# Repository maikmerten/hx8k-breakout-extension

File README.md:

# hx8k-breakout-extension
A PCB with SRAM, buttons, LEDs and some pmod-compatible connectors for the Lattice HX8K Breakout Board

**Please notice**: This PCB only carries SRAM with a data bus width of 8 bits. This is pretty narrow and can be performance-limiting. Also, let's be honest, this PCB layout is somewhat wacky. Perhaps you might consider building [a more recent design with 16-bit SRAM](https://github.com/maikmerten/hx8k-sram16-extension) instead.

## BOM

| Component | Description | Qty. |
|-----------|-------------|------|
| U1 | 4 MBit SRAM chip, 512Kx8, AS7C34096A, 10ns recommended, TSOP-II 44 | 1 |
| RN1, RN2, RN3, RN4, RN5, RN6, RN7, RN8 | 33 Ohm resistor network, 4 resistors in one package, 1206 (4x0603) package | 8 |
| C1 | 100nF ceramic capacitor, 0805 package | 1 |
| D1, D2 | SMD LEDs, red, 0805 package | 2 |
| R1, R2 | resistors for the LEDs, 330 Ohm, 0805 package | 2 |
| SW1, SW2 | 6x6 mm push buttons, THT | 2 |
| R3, R3 | optional pull-ups for SW1 and SW2, anything between 10K and 50K should be fine, 0805 package | 2 |
| J1, J2 | 2x20 male pin headers, 2.54 mm pin spacing | 2 |
| J3, J4 | 2x6 right-angled headers | 2 |
| J5 | 1x6 right-angled header | 1 |

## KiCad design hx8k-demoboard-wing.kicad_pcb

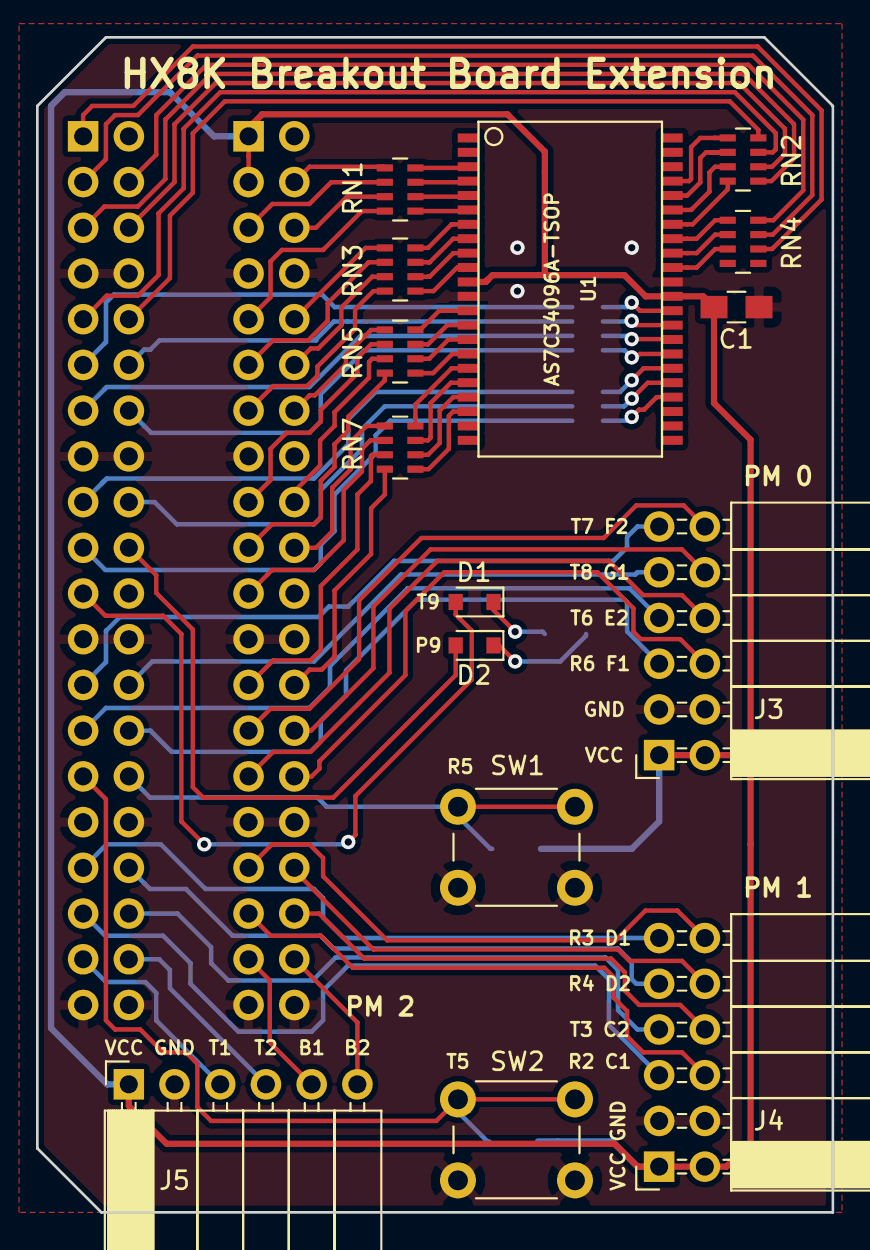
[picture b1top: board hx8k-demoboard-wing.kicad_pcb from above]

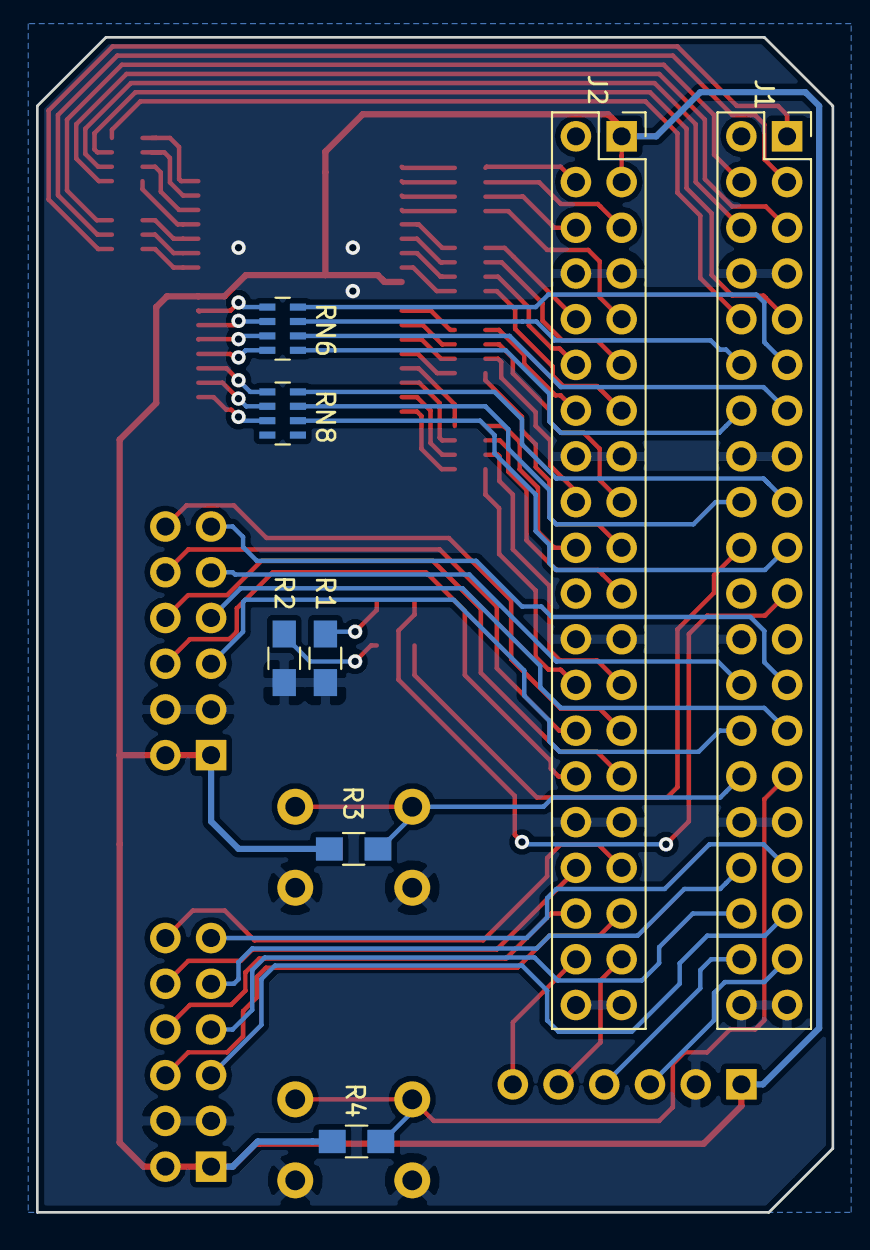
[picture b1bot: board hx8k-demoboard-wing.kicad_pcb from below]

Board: 2 copper layers, 44.2 x 65.3 mm, 23 parts (8 on the bottom side), 88 nets.

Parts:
C1: 100nF; C_0805_HandSoldering
D1, D2: LED; D_0805
J1, J2: Conn_02x20_Odd_Even; Socket_Strip_Straight_2x20_Pitch2.54mm
J3, J4: Conn_02x06_Odd_Even; Socket_Strip_Angled_2x06_Pitch2.54mm
J5: Conn_01x06; Socket_Strip_Angled_1x06_Pitch2.54mm
R1, R2: 300; R_0805_HandSoldering
R3, R4: 10k; R_0805_HandSoldering
RN1, RN2, RN3, RN4, RN5, RN6, RN7, RN8: R_Pack04; R_Array_Concave_4x0603
SW1, SW2: SW_Push; SW_PUSH_6mm
U1: AS7C34096A-TSOP; tsop2-44

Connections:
AD0: RN1.8, U1.3
AD1: RN1.7, U1.4
AD2: RN1.6, U1.5
AD3: RN1.5, U1.6
AD4: RN3.8, U1.7
AD5: RN5.5, U1.16
AD6: RN7.8, U1.17
AD7: RN7.7, U1.18
AD8: RN7.6, U1.19
AD9: RN7.5, U1.20
AD10: RN8.3, U1.26
AD11: RN8.2, U1.27
AD12: RN8.1, U1.28
AD13: RN6.4, U1.29
AD14: RN6.3, U1.30
AD15: RN2.4, U1.38
AD16: RN2.3, U1.39
AD17: RN2.2, U1.40
AD18: RN2.1, U1.41
B1: J2.37, J5.5
B2: J2.38, J5.6
C1: J2.35, J4.6
C2: J2.36, J4.8
CE: RN3.7, U1.8
D1: J2.33, J4.12
D2: J2.34, J4.10
E2: J2.29, J3.8
F1: J2.30, J3.6
F2: J2.27, J3.12
G1: J2.28, J3.10
G2: J2.25, RN7.3
GND: C1.2, J1.7, J1.8, J1.15, J1.16, J1.23, J1.24, J1.31, J1.32, J1.39, J1.40, J2.7, J2.8, J2.15, J2.16, J2.23, J2.24, J2.31, J2.32, J2.39, J2.40, J3.3, J3.4, J4.3, J4.4, J5.2, R1.2, R2.2, SW1.2, SW2.2, U1.12, U1.34
H1: J2.26, RN7.4
H2: J2.21, RN7.2
IO0: RN3.6, U1.9
IO1: RN3.5, U1.10
IO2: RN5.8, U1.13
IO3: RN5.7, U1.14
IO4: RN6.2, U1.31
IO5: RN6.1, U1.32
IO6: RN4.3, U1.35
IO7: RN4.2, U1.36
J1: J2.20, RN7.1
J2: J2.19, RN5.4
K1: J2.18, RN5.3
K3: J2.17, RN5.2
L1: J2.14, RN5.1
L3: J2.13, RN3.4
M1: J2.12, RN3.3
M2: J2.11, RN3.2
M11: J1.12, RN6.7
N2: J2.10, RN3.1
N3: J2.9, RN1.4
N10: J1.11, RN6.8
N12: J1.9, RN2.7
unnamed: D1.1, R1.1
unnamed: D2.1, R2.1
OE: RN4.1, U1.37
P1: J2.5, RN1.2
P2: J2.6, RN1.3
P8: J1.19, RN8.6
P9: D2.2, J1.20
P10: J1.14, RN6.5
P13: J1.10, RN2.8
R1: J2.4, RN1.1
R2: J1.35, J4.5
R3: J1.33, J4.11
R4: J1.34, J4.9
R5: J1.30, R3.1, SW1.1
R6: J1.28, J3.5
R10: J1.18, RN8.7
R16: J1.1, RN4.6
T1: J1.37, J5.3
T2: J1.38, J5.4
T3: J1.36, J4.7
T5: J1.29, R4.1, SW2.1
T6: J1.27, J3.7
T7: J1.25, J3.11
T8: J1.26, J3.9
T9: D1.2, J1.21
T10: J1.17, RN8.8
T11: J1.13, RN6.6
T13: J1.5, RN2.5
T14: J1.6, RN2.6
T15: J1.3, RN4.7
T16: J1.4, RN4.8
VCC33: C1.1, J2.1, J2.3, J3.1, J3.2, J4.1, J4.2, J5.1, R3.2, R4.2, U1.11, U1.33
WE: RN5.6, U1.15

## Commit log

2018-08-08 commit project files
2018-08-08 add an image of the board
2018-08-08 add image to README
2018-08-08 commit gerber files
2018-08-25 add BOM to README
2018-08-28 slight update to README
